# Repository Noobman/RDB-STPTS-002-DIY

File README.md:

RDB-STPTS-002-DIY
=================

3Dprint or CNC extension board for *any* development board (5v or 3.3v logic level)

Further info at www.reprap.org/wiki/RDB-STPTS-002-DIY

Current TODO list:

*rework the 6.3mm fuse footprint (currently does not fit correctly)

*maybe? add led indicators for endstops driven by low Vg(th) mosfet

*maybe? add current limited vcc for endstops headers just in case

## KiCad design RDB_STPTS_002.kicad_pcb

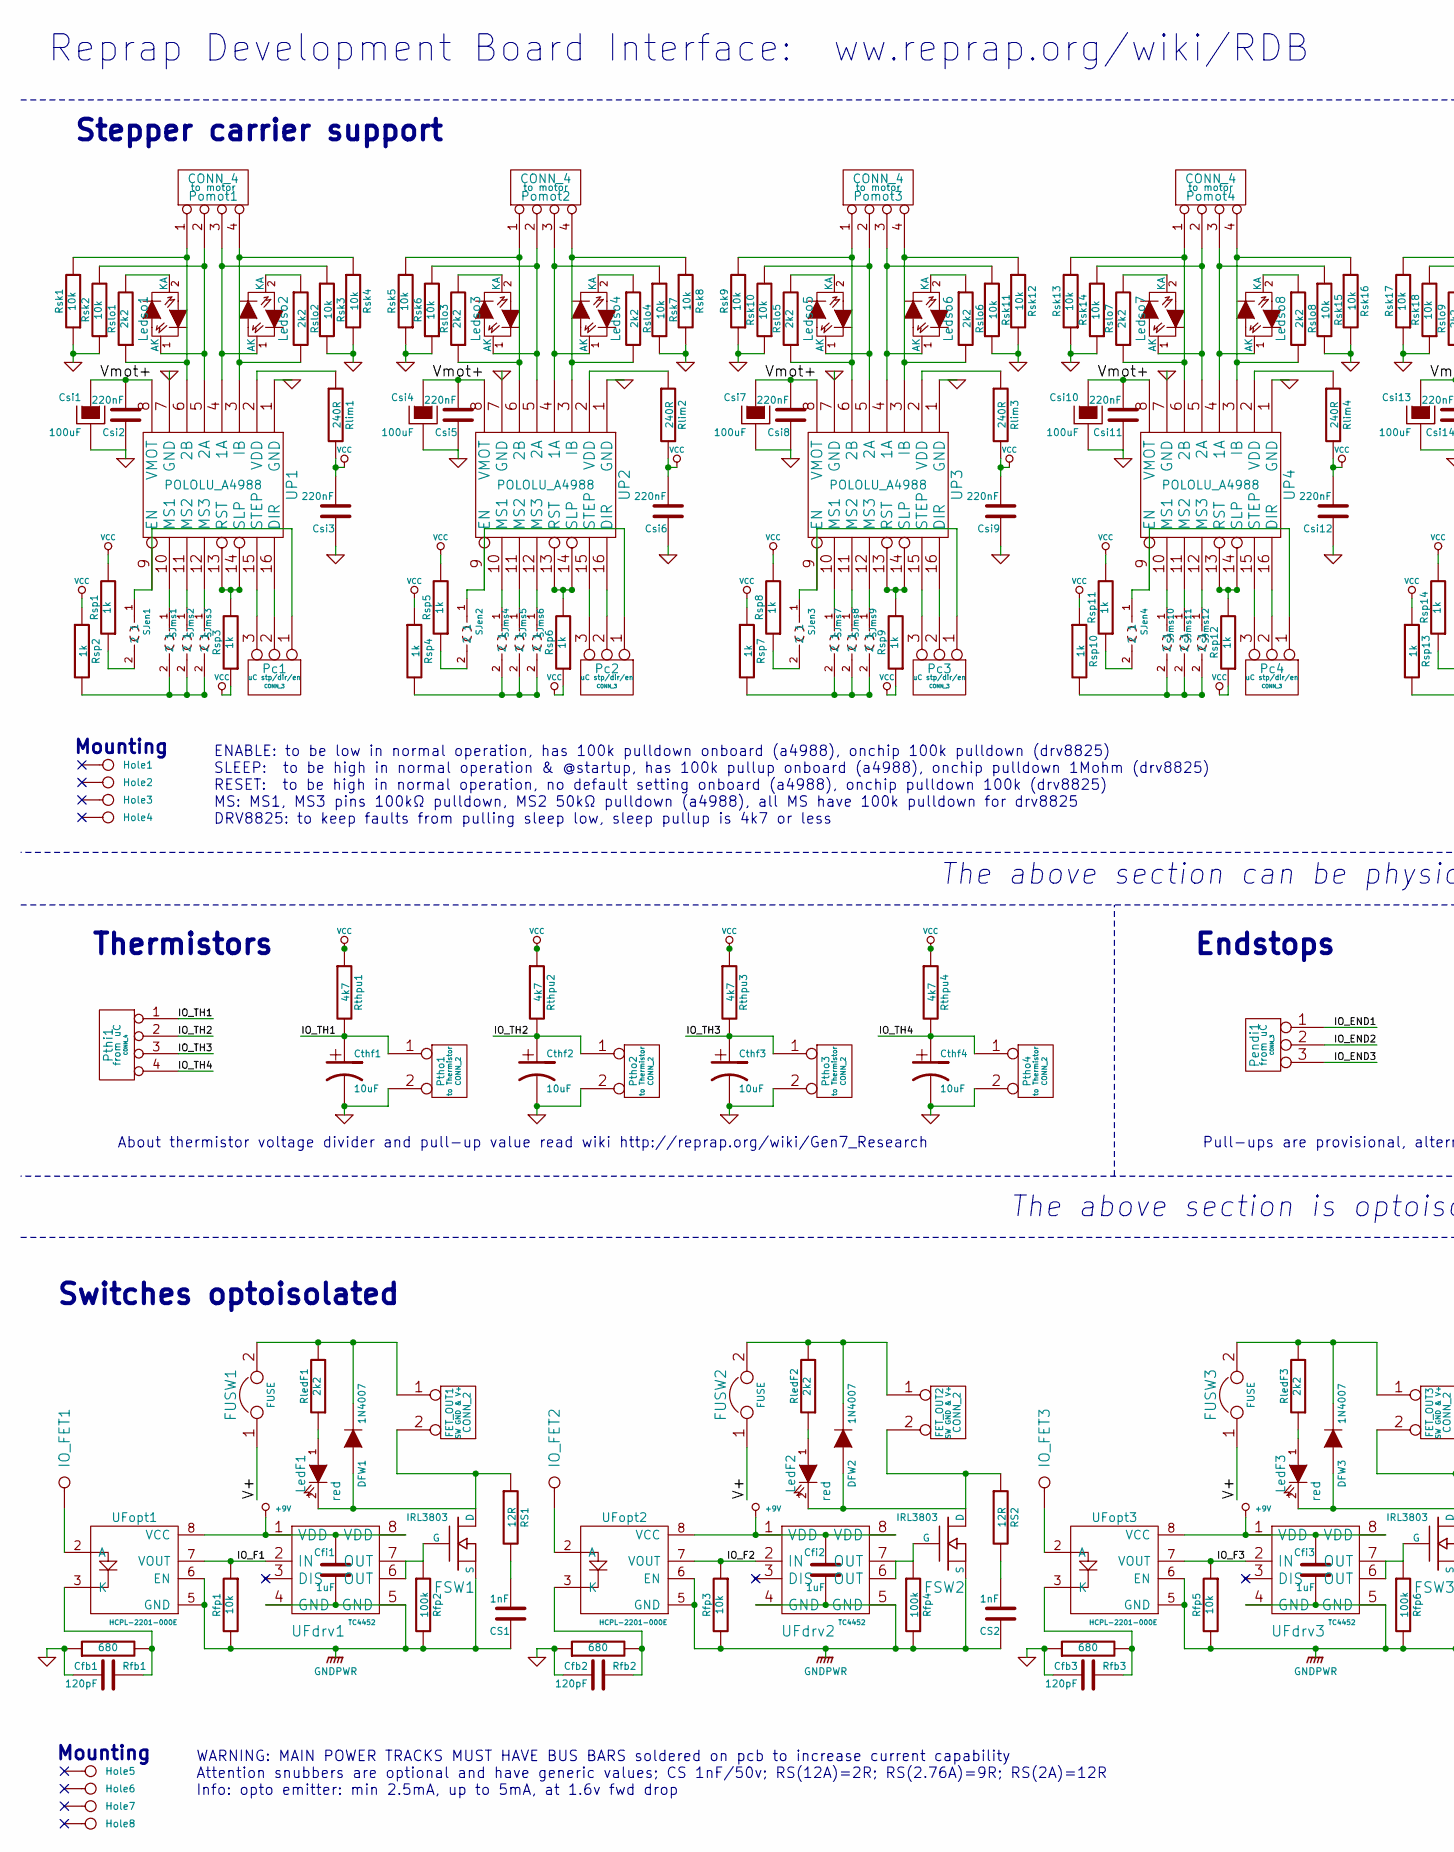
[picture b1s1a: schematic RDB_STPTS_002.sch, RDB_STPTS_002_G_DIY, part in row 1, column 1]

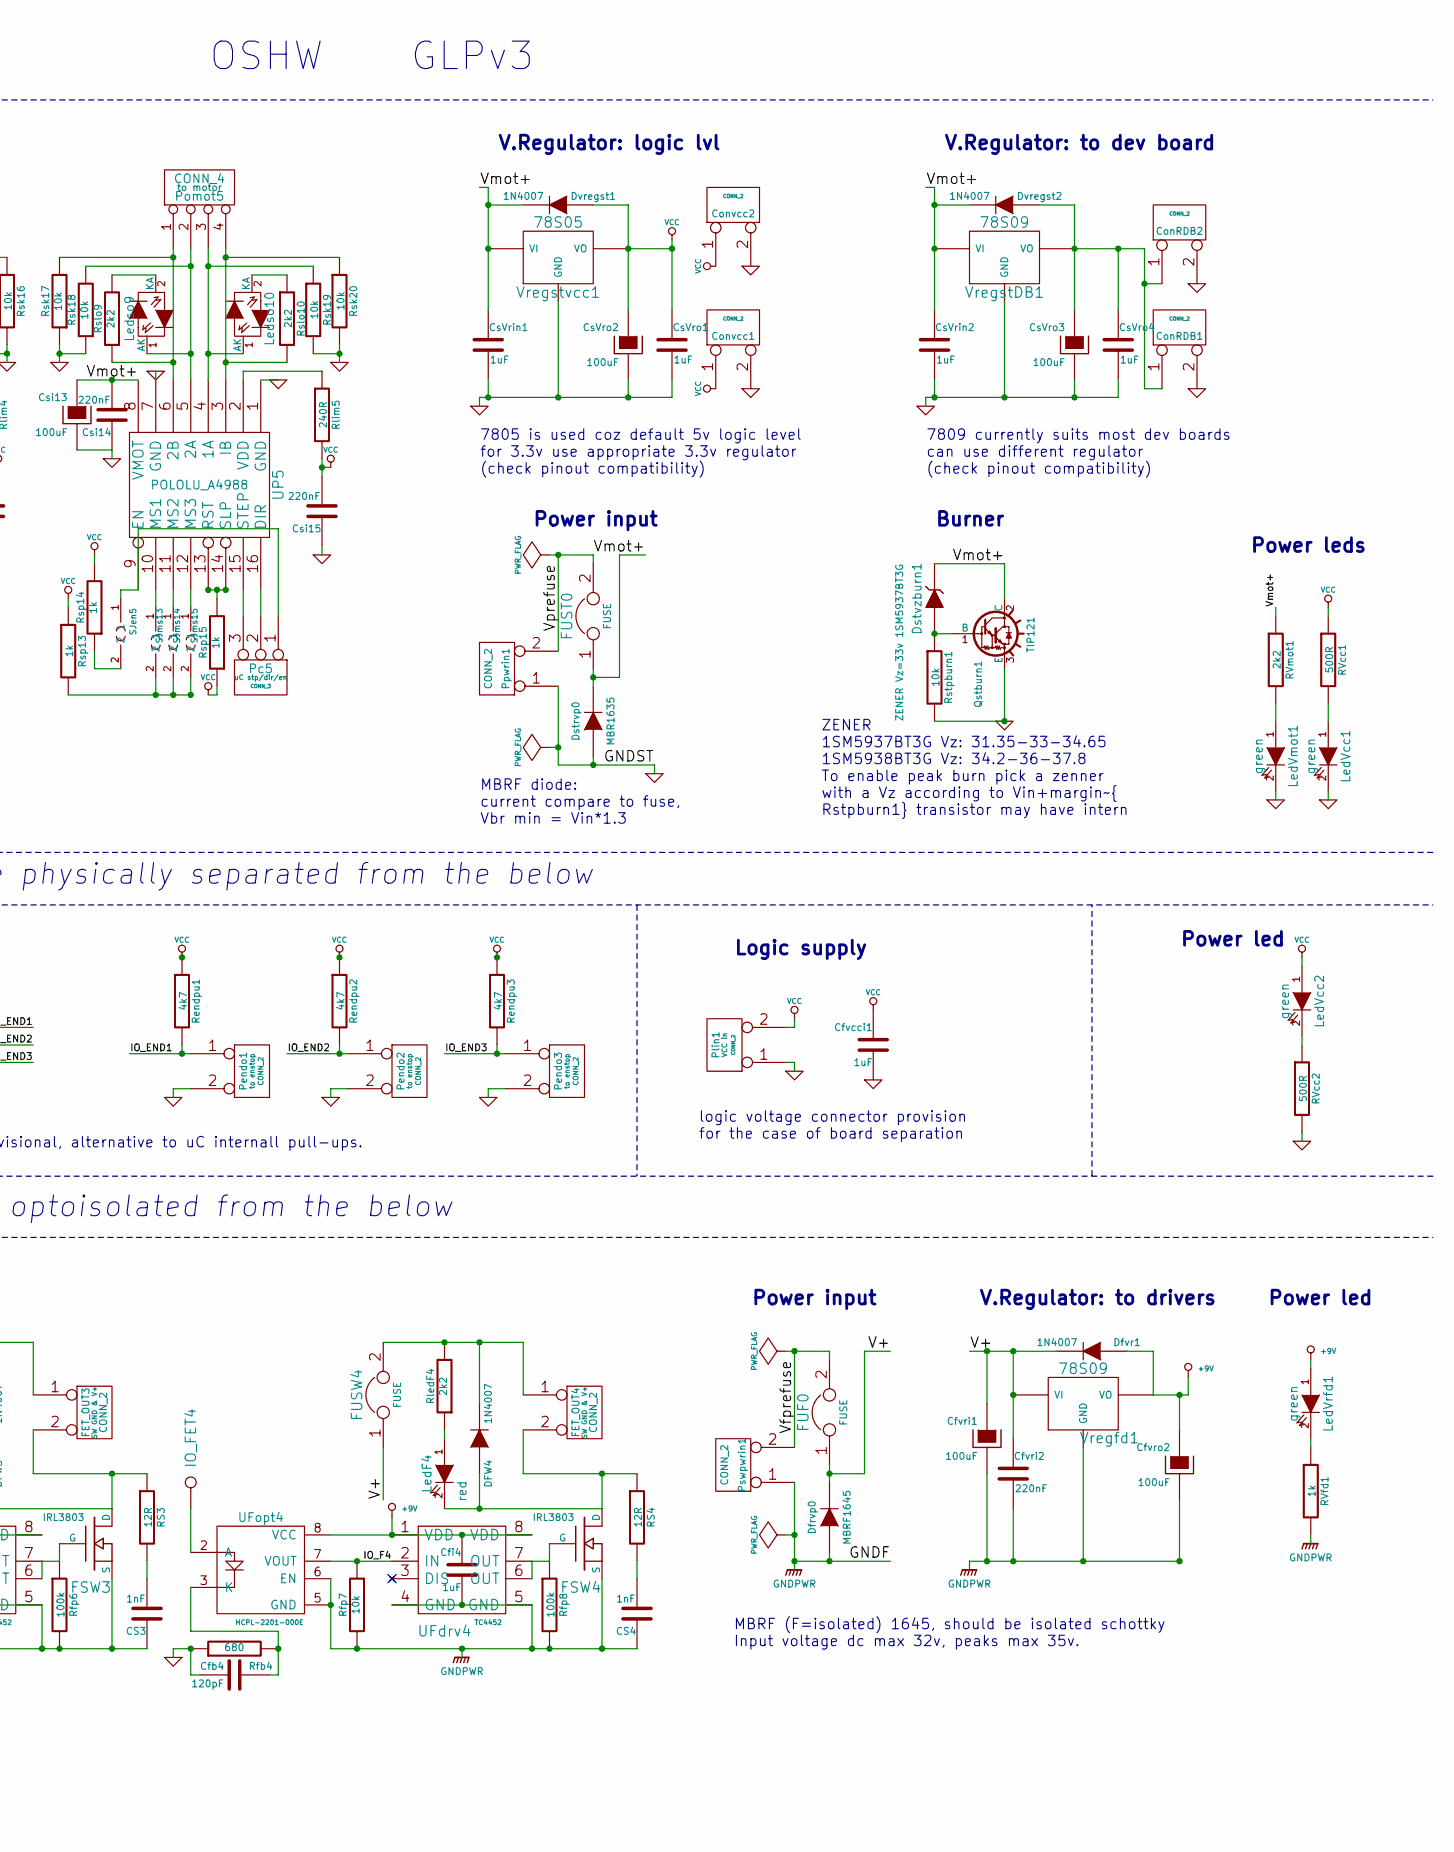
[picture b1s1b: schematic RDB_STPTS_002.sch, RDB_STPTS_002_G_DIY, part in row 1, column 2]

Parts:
CS1, CS2, CS3, CS4: 1nF; Capacitor7x2RM5
Cfb1, Cfb2, Cfb3, Cfb4: 120pF; SMD-1206
Cfi1, Cfi2, Cfi3, Cfi4: 1uF; SM1206
Cfvcci1: 1uF; SM1206
Cfvri1: 100uF; Capacitor8x13RM3.8
Cfvri2: 220nF; SM1206
Cfvro2: 100uF; Capacitor8x13RM3.8
ConRDB1, ConRDB2: CONN_2; SIL-2
Convcc1, Convcc2: CONN_2; SIL-2
CsVrin1, CsVrin2: 1uF; SM1206
CsVro1, CsVro4: 1uF; SM1206
CsVro2, CsVro3: 100uF; Capacitor8x13RM3.8
Csi1, Csi4, Csi7, Csi10, Csi13: 100uF; Capacitor8x13RM3.8
Csi2, Csi3, Csi5, Csi6, Csi8, Csi9, Csi11, Csi12, Csi14, Csi15: 220nF; SM1206
Cthf1, Cthf2, Cthf3, Cthf4: 10uF; Capacitor5x6RM2.5
DFW1, DFW2, DFW3, DFW4: 1N4007; Diode_DO-41_SOD81_Horizontal_RM10
Dfrvp0: MBRF1645; Diode_TO-220_Vertical
Dfvr1: 1N4007; Diode_RM75
Dstrvp0: MBR1635; Diode_TO-220_Vertical
Dstvzburn1: ZENER Vz=33v 1SM5937BT3G; Diode-SMB_Standard
Dvregst1: 1N4007; Diode_DO-41_SOD81_Horizontal_RM10
Dvregst2: 1N4007; Diode_RM75
FET_OUT1, FET_OUT2, FET_OUT3, FET_OUT4: CONN_2; bornier2
FSW1, FSW2, FSW3, FSW4: IRL3803; TO-220_FET-GDS_Vertical_LargePads
FUF0: FUSE; Fuseholder5x20x32_horiz_open_universal_Type-III
FUST0: FUSE; Fuseholder5x20_horiz_open_universal_Type-III
FUSW1, FUSW2, FUSW3, FUSW4: FUSE; Fuseholder5x20_horiz_open_universal_Type-III
Hole1, Hole2, Hole3, Hole4, Hole5, Hole6, Hole7, Hole8: CONN_1; 1pin
IO_FET1, IO_FET2, IO_FET3, IO_FET4: CONN_1; Pin_Header_Straight_1x01
LedF1, LedF2, LedF3, LedF4: red; LED-3MM
LedVcc1, LedVcc2: green; LED-3MM
LedVmot1: green; LED-3MM
LedVrfd1: green; LED-3MM
Ledso1, Ledso2, Ledso3, Ledso4, Ledso5, Ledso6, Ledso7, Ledso8, Ledso9, Ledso10: BI_LED_2_PINS; LED-3MM
Pc1, Pc2, Pc3, Pc4, Pc5: CONN_3; PINHEAD1-3
Pendi1: CONN_3; SIL-3
Pendo1, Pendo2, Pendo3: CONN_2; PINHEAD1-2
Plin1: CONN_2; PINHEAD1-2
Pomot1, Pomot2, Pomot3, Pomot4, Pomot5: CONN_4; PIN_ARRAY_4x1
Ppwrin1: CONN_2; bornier2
Pswpwrin1: CONN_2; bornier2
Pthi1: CONN_4; SIL-4
Ptho1, Ptho2, Ptho3, Ptho4: CONN_2; PINHEAD1-2
Qstburn1: TIP121; TO-220_Neutral123_Vertical
RS1, RS2, RS3, RS4: 12R; Resistor_Horizontal_RM10mm
RVcc1, RVcc2: 500R; SM1206
RVfd1: 1k; SM1206
RVmot1: 2k2; SM1206
Rendpu1, Rendpu2, Rendpu3: 4k7; SM1206
Rfb1, Rfb2, Rfb3, Rfb4: 680; SM1206
Rfp1, Rfp3, Rfp5, Rfp7: 10k; SM1206
Rfp2, Rfp4, Rfp6, Rfp8: 100k; SM1206
RledF1, RledF2, RledF3, RledF4: 2k2; SM1206
Rlim1, Rlim2, Rlim3, Rlim4, Rlim5: 240R; R5
Rsk1, Rsk2, Rsk3, Rsk4, Rsk5, Rsk6, Rsk7, Rsk8, Rsk9, Rsk10, Rsk11, Rsk12, Rsk13, Rsk14, Rsk15, Rsk16, Rsk17, Rsk18, Rsk19, Rsk20: 10k; SM1206
Rslo1, Rslo2, Rslo3, Rslo4, Rslo5, Rslo6, Rslo7, Rslo8, Rslo9, Rslo10: 2k2; SM1206
Rsp1, Rsp2, Rsp3, Rsp4, Rsp5, Rsp6, Rsp7, Rsp8, Rsp9, Rsp10, Rsp11, Rsp12, Rsp13, Rsp14, Rsp15: 1k; SM1206
Rstpburn1: 10k; SM1206
Rthpu1, Rthpu2, Rthpu3, Rthpu4: 4k7; SM1206
SJen1, SJen2, SJen3, SJen4, SJen5: SOLDERJUMPERTRACE; SM0805
SJms1, SJms2, SJms3, SJms4, SJms5, SJms6, SJms7, SJms8, SJms9, SJms10, SJms11, SJms12, SJms13, SJms14, SJms15: SOLDERJUMPERTRACE; SM0805
UFdrv1, UFdrv2, UFdrv3, UFdrv4: TC4452; DIP-8__300_ELL
UFopt1, UFopt2, UFopt3, UFopt4: HCPL-2201-000E; DIP-8__300_ELL
UP1, UP2, UP3, UP4, UP5: POLOLU_A4988; SWDIP8_.6W.pololu
Vregfd1: 78S09; LM78XXV
VregstDB1: 78S09; LM78XXV
Vregstvcc1: 78S05; LM78XXV

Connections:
+9V: Cfi1.1, Cfi2.1, Cfi3.1, Cfi4.1, Cfvro2.1, Dfvr1.1 (A), LedVrfd1.1 (A), UFdrv1.1 (VDD), UFdrv1.8 (VDD), UFdrv2.1 (VDD), UFdrv2.8 (VDD), UFdrv3.1 (VDD), UFdrv3.8 (VDD), UFdrv4.1 (VDD), UFdrv4.8 (VDD), UFopt1.8 (VCC), UFopt2.8 (VCC), UFopt3.8 (VCC), UFopt4.8 (VCC), Vregfd1.VO
/IO_END1: Pendi1.1, Pendo1.1, Rendpu1.2
/IO_END2: Pendi1.2 (PM), Pendo2.1, Rendpu2.2
/IO_END3: Pendi1.3, Pendo3.1, Rendpu3.2
/IO_F1: Rfp1.1, UFdrv1.2 (IN), UFopt1.7 (VOUT)
/IO_F2: Rfp3.1, UFdrv2.2 (IN), UFopt2.7 (VOUT)
/IO_F3: Rfp5.1, UFdrv3.2 (IN), UFopt3.7 (VOUT)
/IO_F4: Rfp7.1, UFdrv4.2 (IN), UFopt4.7 (VOUT)
/IO_TH1: Cthf1.1, Pthi1.1, Ptho1.1, Rthpu1.2
/IO_TH2: Cthf2.1, Pthi1.2, Ptho2.1, Rthpu2.2
/IO_TH3: Cthf3.1, Pthi1.3, Ptho3.1, Rthpu3.2
/IO_TH4: Cthf4.1, Pthi1.4, Ptho4.1, Rthpu4.2
/V+: Cfvri1.1, Cfvri2.1, Dfrvp0.2 (K), Dfvr1.2 (K), FUF0.1, FUSW1.1, FUSW2.1, FUSW3.1, FUSW4.1, Vregfd1.VI
/Vfprefuse: FUF0.2, Pswpwrin1.2 (PM)
/Vmot+: CsVrin1.1, CsVrin2.1, Csi1.1, Csi2.2, Csi4.1, Csi5.2, Csi7.1, Csi8.2, Csi10.1, Csi11.2, Csi13.1, Csi14.2, Dstrvp0.2 (K), Dstvzburn1.2 (K), Dvregst1.2 (K), Dvregst2.2 (K), FUST0.1, Qstburn1.2 (C), RVmot1.1, UP1.8 (VMOT), UP2.8 (VMOT), UP3.8 (VMOT), UP4.8 (VMOT), UP5.8 (VMOT), VregstDB1.VI, Vregstvcc1.VI
/Vprefuse: FUST0.2, Ppwrin1.2 (PM)
GND: Cfb1.2, Cfb2.2, Cfb3.2, Cfb4.2, Cfvcci1.2, ConRDB1.2 (PM), ConRDB2.2 (PM), Convcc1.2 (PM), Convcc2.2 (PM), CsVrin1.2, CsVrin2.2, CsVro1.2, CsVro2.2, CsVro3.2, CsVro4.2, Csi1.2, Csi2.1, Csi3.1, Csi4.2, Csi5.1, Csi6.1, Csi7.2, Csi8.1, Csi9.1, Csi10.2, Csi11.1, Csi12.1, Csi13.2, Csi14.1, Csi15.1, Cthf1.2, Cthf2.2, Cthf3.2, Cthf4.2, Dstrvp0.1 (A), LedVcc1.2 (K), LedVmot1.2 (K), Pendo1.2 (PM), Pendo2.2 (PM), Pendo3.2 (PM), Plin1.1, Ppwrin1.1, Ptho1.2 (PM), Ptho2.2 (PM), Ptho3.2 (PM), Ptho4.2 (PM), Qstburn1.3 (E), RVcc2.2, Rfb1.1, Rfb2.1, Rfb3.1, Rfb4.1, Rsk1.1, Rsk2.1, Rsk3.2, Rsk4.2, Rsk5.1, Rsk6.1, Rsk7.2, Rsk8.2, Rsk9.1, Rsk10.1, Rsk11.2, Rsk12.2, Rsk13.1, Rsk14.1, Rsk15.2, Rsk16.2, Rsk17.1, Rsk18.1, Rsk19.2, Rsk20.2, Rstpburn1.2, UP1.1 (GND), UP1.7 (GND), UP2.1 (GND), UP2.7 (GND), UP3.1 (GND), UP3.7 (GND), UP4.1 (GND), UP4.7 (GND), UP5.1 (GND), UP5.7 (GND), VregstDB1.GND, Vregstvcc1.GND
GNDPWR: CS1.1, CS2.1, CS3.1, CS4.1, Cfi1.2, Cfi2.2, Cfi3.2, Cfi4.2, Cfvri1.2, Cfvri2.2, Cfvro2.2, Dfrvp0.1 (A), FSW1.S, FSW2.S, FSW3.S, FSW4.S, Pswpwrin1.1, RVfd1.2, Rfp1.2, Rfp2.2, Rfp3.2, Rfp4.2, Rfp5.2, Rfp6.2, Rfp7.2, Rfp8.2, UFdrv1.4 (GND), UFdrv1.5 (GND), UFdrv2.4 (GND), UFdrv2.5 (GND), UFdrv3.4 (GND), UFdrv3.5 (GND), UFdrv4.4 (GND), UFdrv4.5 (GND), UFopt1.5 (GND), UFopt1.6 (EN), UFopt2.5 (GND), UFopt2.6 (EN), UFopt3.5 (GND), UFopt3.6 (EN), UFopt4.5 (GND), UFopt4.6 (EN), Vregfd1.GND
unnamed: CS1.2, RS1.2
unnamed: CS2.2, RS2.2
unnamed: CS3.2, RS3.2
unnamed: CS4.2, RS4.2
unnamed: Cfb1.1, Rfb1.2, UFopt1.3 (K)
unnamed: Cfb2.1, Rfb2.2, UFopt2.3 (K)
unnamed: Cfb3.1, Rfb3.2, UFopt3.3 (K)
unnamed: Cfb4.1, Rfb4.2, UFopt4.3 (K)
unnamed: ConRDB1.1, ConRDB2.1, CsVro3.1, CsVro4.1, Dvregst2.1 (A), VregstDB1.VO
unnamed: DFW1.1 (A), FET_OUT1.2 (PM), FSW1.D, LedF1.2 (K), RS1.1
unnamed: DFW1.2 (K), FET_OUT1.1, FUSW1.2, RledF1.2
unnamed: DFW2.1 (A), FET_OUT2.2 (PM), FSW2.D, LedF2.2 (K), RS2.1
unnamed: DFW2.2 (K), FET_OUT2.1, FUSW2.2, RledF2.2
unnamed: DFW3.1 (A), FET_OUT3.2 (PM), FSW3.D, LedF3.2 (K), RS3.1
unnamed: DFW3.2 (K), FET_OUT3.1, FUSW3.2, RledF3.2
unnamed: DFW4.1 (A), FET_OUT4.2 (PM), FSW4.D, LedF4.2 (K), RS4.1
unnamed: DFW4.2 (K), FET_OUT4.1, FUSW4.2, RledF4.2
unnamed: Dstvzburn1.1 (A), Qstburn1.1 (B), Rstpburn1.1
unnamed: FSW1.G, Rfp2.1, UFdrv1.6 (OUT), UFdrv1.7 (OUT)
unnamed: FSW2.G, Rfp4.1, UFdrv2.6 (OUT), UFdrv2.7 (OUT)
unnamed: FSW3.G, Rfp6.1, UFdrv3.6 (OUT), UFdrv3.7 (OUT)
unnamed: FSW4.G, Rfp8.1, UFdrv4.6 (OUT), UFdrv4.7 (OUT)
unnamed: IO_FET1.1, UFopt1.2 (A)
unnamed: IO_FET2.1, UFopt2.2 (A)
unnamed: IO_FET3.1, UFopt3.2 (A)
unnamed: IO_FET4.1, UFopt4.2 (A)
unnamed: LedF1.1 (A), RledF1.1
unnamed: LedF2.1 (A), RledF2.1
unnamed: LedF3.1 (A), RledF3.1
unnamed: LedF4.1 (A), RledF4.1
unnamed: LedVcc1.1 (A), RVcc1.2
unnamed: LedVcc2.2 (K), RVcc2.1
unnamed: LedVmot1.1 (A), RVmot1.2
unnamed: LedVrfd1.2 (K), RVfd1.1
unnamed: Ledso1.1 (AK), Pomot1.2, Rsk2.2, UP1.5 (2A)
unnamed: Ledso1.2 (KA), Rslo1.2
unnamed: Ledso2.1 (AK), Pomot1.3, Rsk3.1, UP1.4 (1A)
unnamed: Ledso2.2 (KA), Rslo2.1
unnamed: Ledso3.1 (AK), Pomot2.2, Rsk6.2, UP2.5 (2A)
unnamed: Ledso3.2 (KA), Rslo3.2
unnamed: Ledso4.1 (AK), Pomot2.3, Rsk7.1, UP2.4 (1A)
unnamed: Ledso4.2 (KA), Rslo4.1
unnamed: Ledso5.1 (AK), Pomot3.2, Rsk10.2, UP3.5 (2A)
unnamed: Ledso5.2 (KA), Rslo5.2
unnamed: Ledso6.1 (AK), Pomot3.3, Rsk11.1, UP3.4 (1A)
unnamed: Ledso6.2 (KA), Rslo6.1
unnamed: Ledso7.1 (AK), Pomot4.2, Rsk14.2, UP4.5 (2A)
unnamed: Ledso7.2 (KA), Rslo7.2
unnamed: Ledso8.1 (AK), Pomot4.3, Rsk15.1, UP4.4 (1A)
unnamed: Ledso8.2 (KA), Rslo8.1
unnamed: Ledso9.1 (AK), Pomot5.2, Rsk18.2, UP5.5 (2A)
unnamed: Ledso9.2 (KA), Rslo9.2
unnamed: Ledso10.1 (AK), Pomot5.3, Rsk19.1, UP5.4 (1A)
unnamed: Ledso10.2 (KA), Rslo10.1
unnamed: Pc1.1, SJen1.1, UP1.9 (EN)
unnamed: Pc1.2 (PM), UP1.16 (DIR)
unnamed: Pc1.3, UP1.15 (STEP)
unnamed: Pc2.1, SJen2.1, UP2.9 (EN)
unnamed: Pc2.2 (PM), UP2.16 (DIR)
unnamed: Pc2.3, UP2.15 (STEP)
unnamed: Pc3.1, SJen3.1, UP3.9 (EN)
unnamed: Pc3.2 (PM), UP3.16 (DIR)
unnamed: Pc3.3, UP3.15 (STEP)
unnamed: Pc4.1, SJen4.1, UP4.9 (EN)
unnamed: Pc4.2 (PM), UP4.16 (DIR)
unnamed: Pc4.3, UP4.15 (STEP)
unnamed: Pc5.1, SJen5.1, UP5.9 (EN)
unnamed: Pc5.2 (PM), UP5.16 (DIR)
unnamed: Pc5.3, UP5.15 (STEP)
unnamed: Pomot1.1, Rsk1.2, Rslo1.1, UP1.6 (2B)
unnamed: Pomot1.4, Rsk4.1, Rslo2.2, UP1.3 (IB)
unnamed: Pomot2.1, Rsk5.2, Rslo3.1, UP2.6 (2B)
unnamed: Pomot2.4, Rsk8.1, Rslo4.2, UP2.3 (IB)
unnamed: Pomot3.1, Rsk9.2, Rslo5.1, UP3.6 (2B)
unnamed: Pomot3.4, Rsk12.1, Rslo6.2, UP3.3 (IB)
unnamed: Pomot4.1, Rsk13.2, Rslo7.1, UP4.6 (2B)
unnamed: Pomot4.4, Rsk16.1, Rslo8.2, UP4.3 (IB)
unnamed: Pomot5.1, Rsk17.2, Rslo9.1, UP5.6 (2B)
unnamed: Pomot5.4, Rsk20.1, Rslo10.2, UP5.3 (IB)
unnamed: Rlim1.1, UP1.2 (VDD)
unnamed: Rlim2.1, UP2.2 (VDD)
unnamed: Rlim3.1, UP3.2 (VDD)
unnamed: Rlim4.1, UP4.2 (VDD)
unnamed: Rlim5.1, UP5.2 (VDD)
unnamed: Rsp1.1, SJen1.2
unnamed: Rsp2.2, SJms1.2, SJms2.2, SJms3.2
unnamed: Rsp3.2, UP1.13 (RST), UP1.14 (SLP)
unnamed: Rsp4.2, SJms4.2, SJms5.2, SJms6.2
unnamed: Rsp5.1, SJen2.2
unnamed: Rsp6.2, UP2.13 (RST), UP2.14 (SLP)
unnamed: Rsp7.2, SJms7.2, SJms8.2, SJms9.2
unnamed: Rsp8.1, SJen3.2
unnamed: Rsp9.2, UP3.13 (RST), UP3.14 (SLP)
unnamed: Rsp10.2, SJms10.2, SJms11.2, SJms12.2
unnamed: Rsp11.1, SJen4.2
unnamed: Rsp12.2, UP4.13 (RST), UP4.14 (SLP)
unnamed: Rsp13.2, SJms13.2, SJms14.2, SJms15.2
unnamed: Rsp14.1, SJen5.2
unnamed: Rsp15.2, UP5.13 (RST), UP5.14 (SLP)
unnamed: SJms1.1, UP1.10 (MS1)
unnamed: SJms2.1, UP1.11 (MS2)
unnamed: SJms3.1, UP1.12 (MS3)
unnamed: SJms4.1, UP2.10 (MS1)
unnamed: SJms5.1, UP2.11 (MS2)
unnamed: SJms6.1, UP2.12 (MS3)
unnamed: SJms7.1, UP3.10 (MS1)
unnamed: SJms8.1, UP3.11 (MS2)
unnamed: SJms9.1, UP3.12 (MS3)
unnamed: SJms10.1, UP4.10 (MS1)
unnamed: SJms11.1, UP4.11 (MS2)
unnamed: SJms12.1, UP4.12 (MS3)
unnamed: SJms13.1, UP5.10 (MS1)
unnamed: SJms14.1, UP5.11 (MS2)
unnamed: SJms15.1, UP5.12 (MS3)
VCC: Cfvcci1.1, Convcc1.1, Convcc2.1, CsVro1.1, CsVro2.1, Csi3.2, Csi6.2, Csi9.2, Csi12.2, Csi15.2, Dvregst1.1 (A), LedVcc2.1 (A), Plin1.2 (PM), RVcc1.1, Rendpu1.1, Rendpu2.1, Rendpu3.1, Rlim1.2, Rlim2.2, Rlim3.2, Rlim4.2, Rlim5.2, Rsp1.2, Rsp2.1, Rsp3.1, Rsp4.1, Rsp5.2, Rsp6.1, Rsp7.1, Rsp8.2, Rsp9.1, Rsp10.1, Rsp11.2, Rsp12.1, Rsp13.1, Rsp14.2, Rsp15.1, Rthpu1.1, Rthpu2.1, Rthpu3.1, Rthpu4.1, Vregstvcc1.VO

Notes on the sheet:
Reprap Development Board Interface: ww.reprap.org/wiki/RDB
GLPv3
Power input
V.Regulator: logic lvl
Power leds
7805 is used coz default 5v logic level for 3.3v use appropriate 3.3v regulator (check pinout compatibility)
MBRF diode: current compare to fuse, Vbr min = Vin*1.3
OSHW
Mounting
ENABLE: to be low in normal operation, has 100k pulldown onboard (a4988), onchip 100k pulldown (drv8825) SLEEP: to be high in normal operation & @startup, has 100k pullup onboard (a4988), onchip pulldown 1Mohm (drv8825) RESET: to be high in normal operation, no default setting onboard (a4988), onch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
WARNING: MAIN POWER TRACKS MUST HAVE BUS BARS soldered on pcb to increase current capability Attention snubbers are optional and have generic values; CS 1nF/50v; RS(12A)=2R; RS(2.76A)=9R; RS(2A)=12R Info: opto emitter: min 2.5mA, up to 5mA, at 1.6v fwd drop
V.Regulator: to dev board
Burner
ZENER 1SM5937BT3G Vz: 31.35-33-34.65 1SM5938BT3G Vz: 34.2-36-37.8 To enable peak burn pick a zenner with a Vz according to Vin+margin~ Rstpburn1 transistor may have intern
Thermistors
Endstops
V.Regulator: to drivers
Switches optoisolated
The above section is optoisolated from the below
Stepper carrier support
The above section can be physically separated from the below
Logic supply
Power led
About thermistor voltage divider and pull-up value read wiki http://reprap.org/wiki/Gen7_Research
Pull-ups are provisional, alternative to uC internall pull-ups.
MBRF (F=isolated) 1645, should be isolated schottky Input voltage dc max 32v, peaks max 35v.
7809 currently suits most dev boards can use different regulator (check pinout compatibility)
logic voltage connector provision for the case of board separation

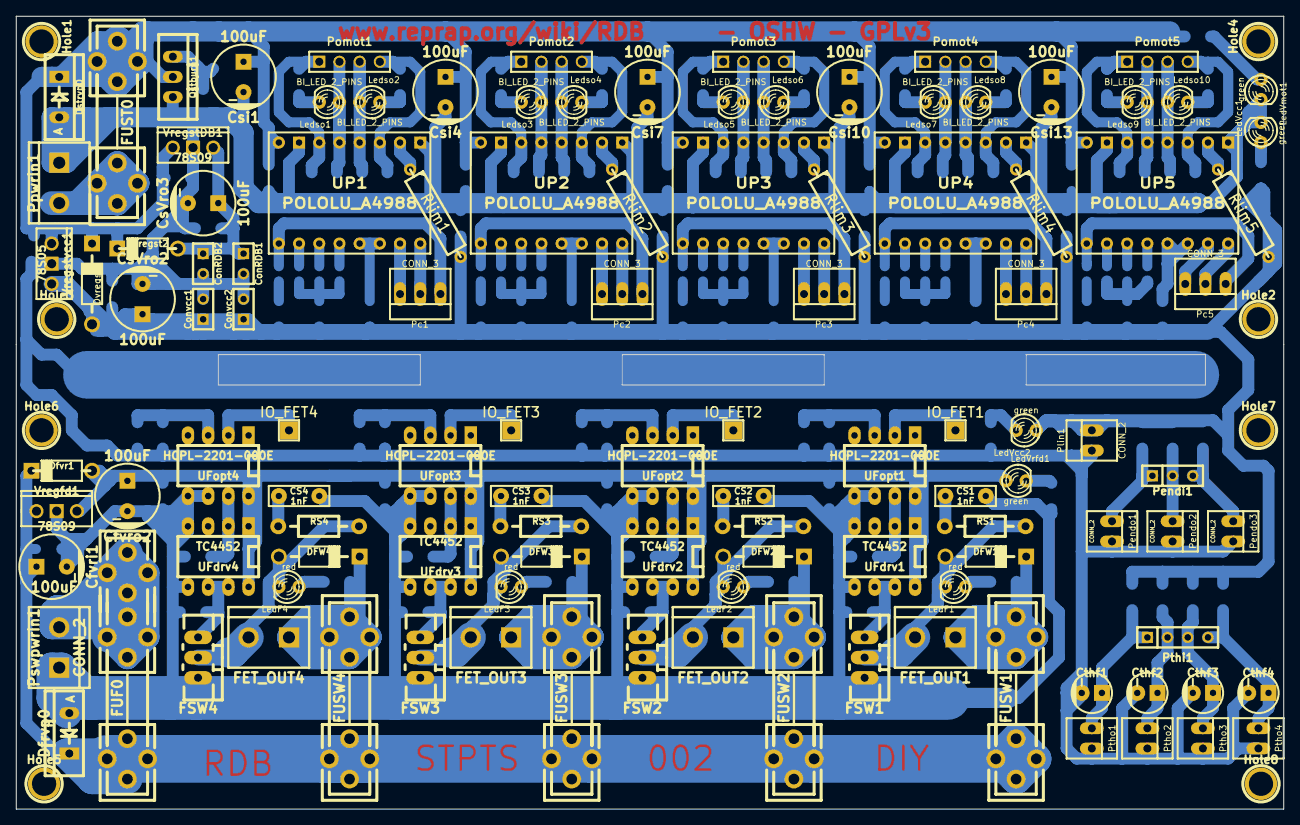
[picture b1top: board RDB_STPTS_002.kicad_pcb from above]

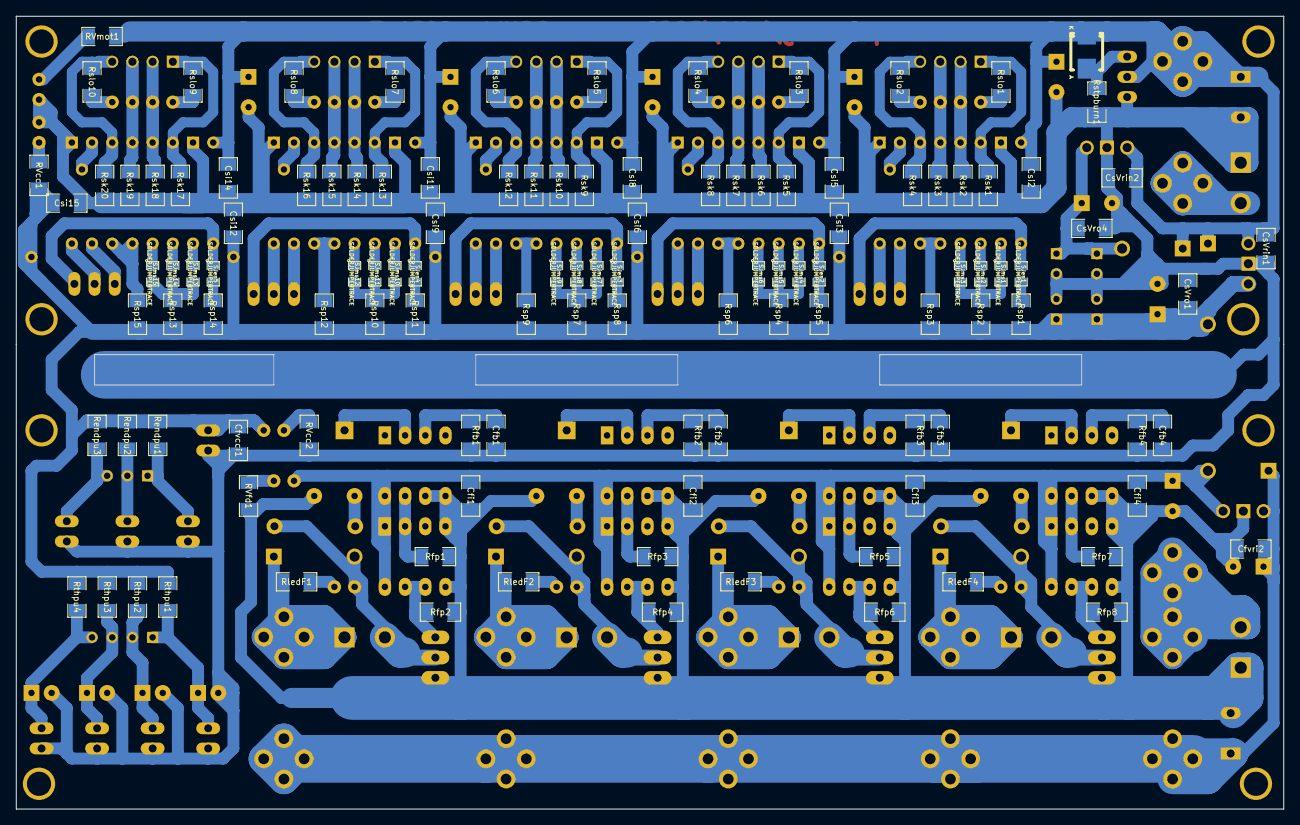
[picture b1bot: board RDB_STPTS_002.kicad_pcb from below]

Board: 2 copper layers, 159.4 x 99.7 mm, 240 parts (118 on the bottom side), 133 nets.

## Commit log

2014-09-26 initial
2014-09-26 cleanup

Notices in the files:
RDB_STPTS_002.kicad_pcb:
www.reprap.org/wiki/RDB - OSHW - GPLv3
